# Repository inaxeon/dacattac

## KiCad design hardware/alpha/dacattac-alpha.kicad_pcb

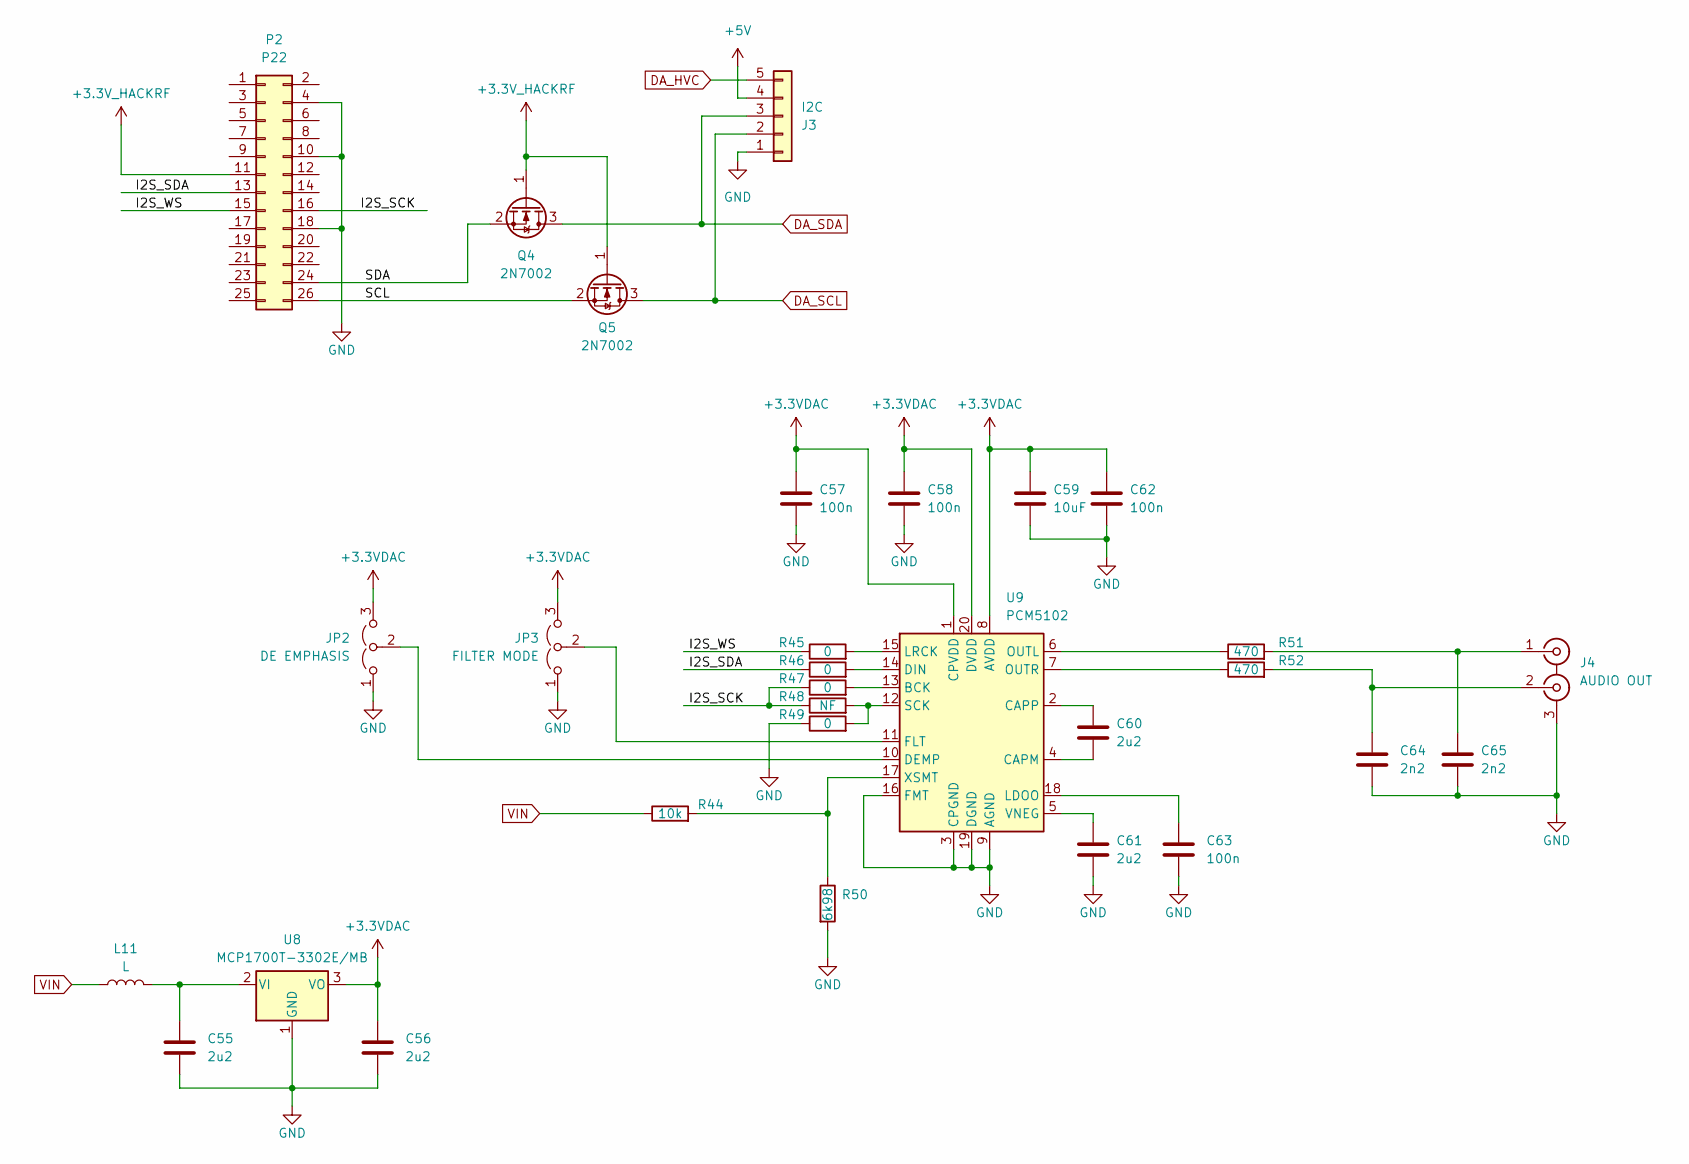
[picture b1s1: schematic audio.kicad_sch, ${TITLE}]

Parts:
C55, C56, C60, C61: 2u2; C_0603_1608Metric
C57, C58, C62, C63: 100n; C_0603_1608Metric
C59: 10uF; C_1210_3225Metric
C64, C65: 2n2; C_0603_1608Metric
J3: I2C; Molex_KK-254_AE-6410-05A_1x05_P2.54mm_Vertical
J4: AUDIO OUT; PJRAN2X1U01X
JP2: DE EMPHASIS; SolderJumper-3_P1.3mm_Open_Pad1.0x1.5mm
JP3: FILTER MODE; SolderJumper-3_P1.3mm_Open_Pad1.0x1.5mm
L11: L; L_1210_3225Metric
P2: P22; GSG-HEADER-2x13
Q4, Q5: 2N7002; SOT-23
R44: 10k; R_0603_1608Metric
R45, R46, R47, R49: 0; R_0603_1608Metric
R48: NF; R_0603_1608Metric
R50: 6k98; R_0603_1608Metric
R51, R52: 470; R_0603_1608Metric
U8: MCP1700T-3302E/MB; SOT-89-3
U9: PCM5102; TSSOP-20_4.4x6.5mm_P0.65mm

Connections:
+3.3VDAC: C56.1, C57.1, C58.1, C59.1, C62.1, JP2.3 (B), JP3.3 (B), U8.3 (VO), U9.1 (CPVDD), U9.8 (AVDD), U9.20 (DVDD)
+3.3V_HACKRF: P2.11, Q4.1 (G), Q5.1 (G); also elsewhere on the board
+5V: J3.4; also elsewhere on the board
/audio/I2S_SCK: P2.16, R47.1, R48.1
/audio/I2S_SDA: P2.13, R46.1
/audio/I2S_WS: P2.15, R45.1
/audio/SCL: P2.26, Q5.2 (S)
/audio/SDA: P2.24, Q4.2 (S)
DA_HVC: J3.5; also elsewhere on the board
DA_SCL: J3.2, Q5.3 (D); also elsewhere on the board
DA_SDA: J3.3, Q4.3 (D); also elsewhere on the board
GND: C55.2, C56.2, C57.2, C58.2, C59.2, C61.2, C62.2, C63.2, C64.2, C65.2, J3.1, J4.3 (EXT), JP2.1 (A), JP3.1 (A), P2.4, P2.10, P2.18, R49.1, R50.2, U8.1 (GND), U9.3 (CPGND), U9.9 (AGND), U9.16 (FMT), U9.19 (DGND); also elsewhere on the board
unnamed: C65.1, J4.1 (IN1), R51.2
unnamed: C64.1, J4.2 (IN2), R52.2
unnamed: JP2.2 (C), U9.10 (DEMP)
unnamed: JP3.2 (C), U9.11 (FLT)
unnamed: C55.1, L11.2, U8.2 (VI)
unnamed: R47.2, U9.13 (BCK)
unnamed: C60.2, U9.4 (CAPM)
unnamed: C60.1, U9.2 (CAPP)
unnamed: R46.2, U9.14 (DIN)
unnamed: C63.1, U9.18 (LDOO)
unnamed: R45.2, U9.15 (LRCK)
unnamed: R51.1, U9.6 (OUTL)
unnamed: R52.1, U9.7 (OUTR)
unnamed: R48.2, R49.2, U9.12 (SCK)
unnamed: C61.1, U9.5 (VNEG)
unnamed: R44.2, R50.1, U9.17 (XSMT)
VIN: L11.1, R44.1; also elsewhere on the board

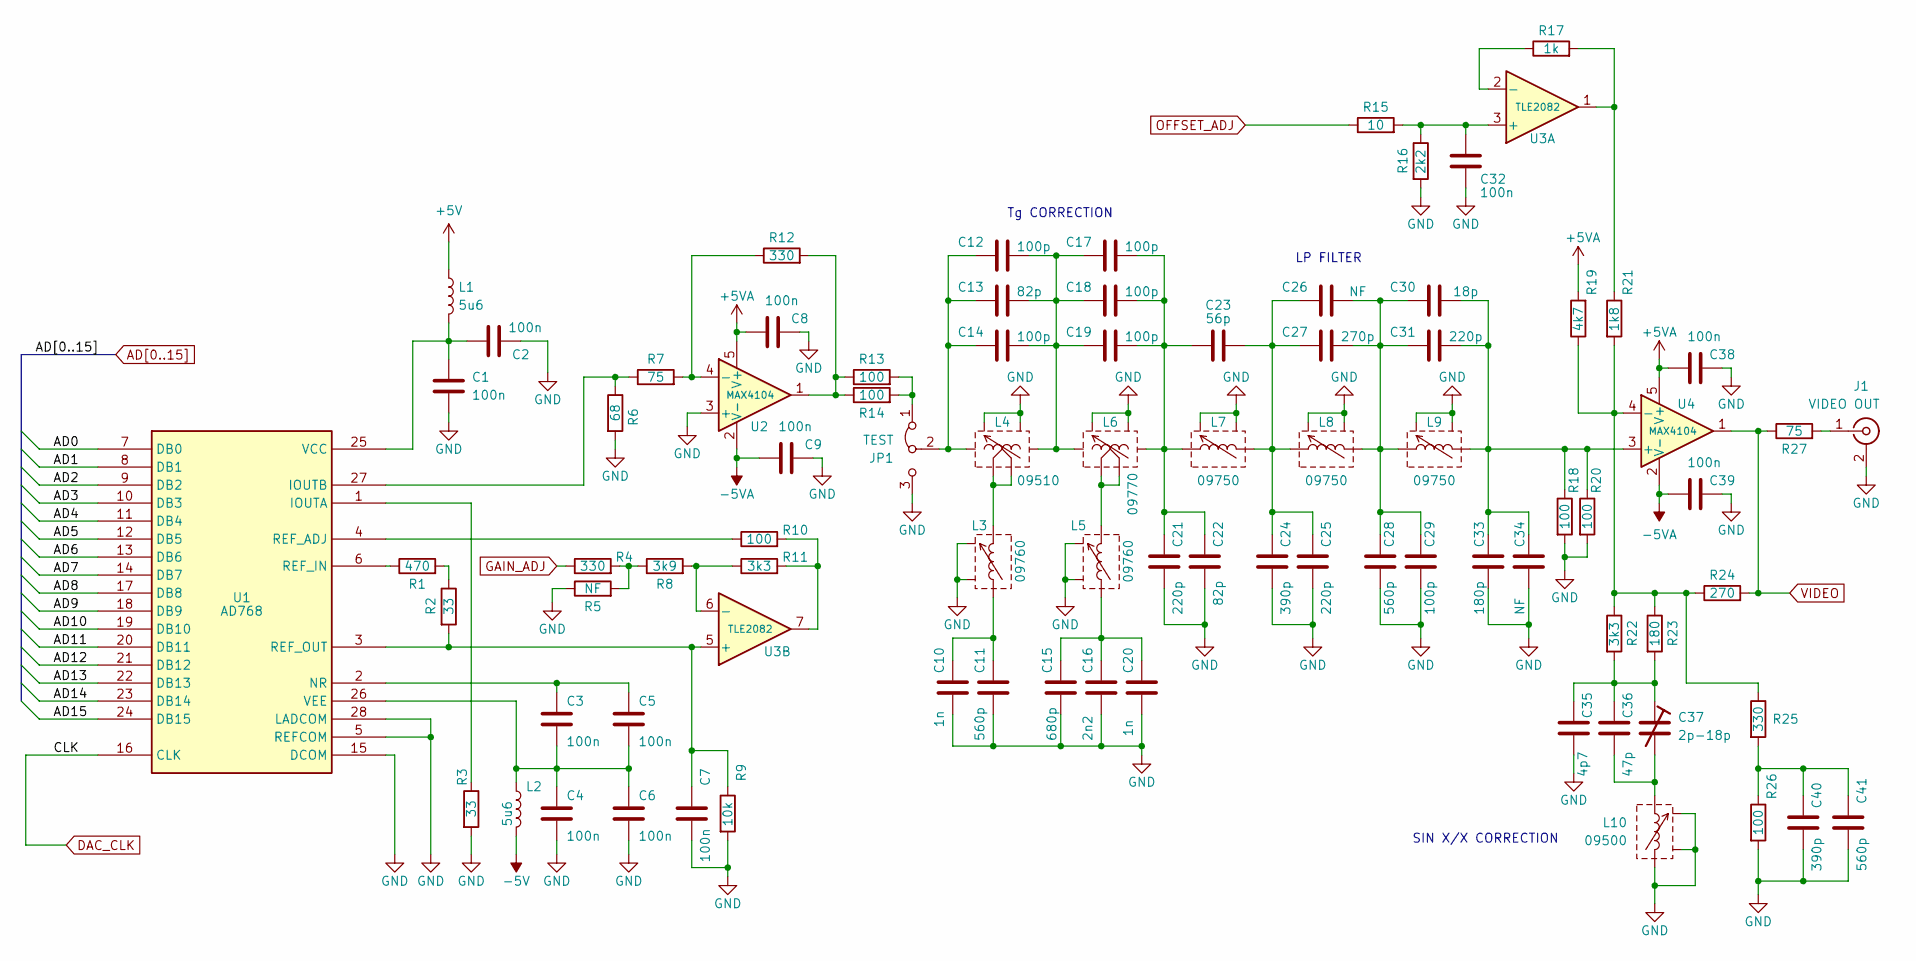
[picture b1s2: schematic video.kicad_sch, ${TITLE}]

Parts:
C1, C2, C3, C4, C5, C6, C7, C8, C9, C32, C38, C39: 100n; C_0603_1608Metric
C10, C20: 1n; C_0603_1608Metric
C11, C28, C41: 560p; C_0603_1608Metric
C12, C14, C17, C18, C19, C29: 100p; C_0603_1608Metric
C13, C22: 82p; C_0603_1608Metric
C15: 680p; C_0603_1608Metric
C16: 2n2; C_0603_1608Metric
C21, C25, C31: 220p; C_0603_1608Metric
C23: 56p; C_0603_1608Metric
C24, C40: 390p; C_0603_1608Metric
C26, C34: NF; C_0603_1608Metric
C27: 270p; C_0603_1608Metric
C30: 18p; C_0603_1608Metric
C33: 180p; C_0603_1608Metric
C35: 4p7; C_0603_1608Metric
C36: 47p; C_0603_1608Metric
C37: 2p-18p; BFC2808xxxxx
J1: VIDEO OUT; 731010120
JP1: TEST; PinHeader_1x03_P2.54mm_Vertical
L1, L2: 5u6; L_1210_3225Metric
L3, L5: 09760; NEOSID_7MM
L4: 09510; NEOSID_7MM
L6: 09770; NEOSID_7MM
L7, L8, L9: 09750; NEOSID_7MM
L10: 09500; NEOSID_7MM
R1: 470; R_0603_1608Metric
R2, R3: 33; R_0603_1608Metric
R4, R12, R25: 330; R_0603_1608Metric
R5: NF; R_0603_1608Metric
R6: 68; R_0603_1608Metric
R7, R27: 75; R_0603_1608Metric
R8: 3k9; R_0603_1608Metric
R9: 10k; R_0603_1608Metric
R10, R13, R14, R18, R20, R26: 100; R_0603_1608Metric
R11, R22: 3k3; R_0603_1608Metric
R15: 10; R_0603_1608Metric
R16: 2k2; R_0603_1608Metric
R17: 1k; R_0603_1608Metric
R19: 4k7; R_0603_1608Metric
R21: 1k8; R_0603_1608Metric
R23: 180; R_0603_1608Metric
R24: 270; R_0603_1608Metric
U1: AD768; SOIC-28W_7.5x18.7mm_P1.27mm
U2, U4: MAX4104; SOT-23-5
U3: TLE2082; SOIC-8_3.9x4.9mm_P1.27mm

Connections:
+5V: L1.1; also elsewhere on the board
+5VA: C8.1, C38.1, R19.2, U2.5 (V+), U4.5 (V+); also elsewhere on the board
-5V: L2.2; also elsewhere on the board
-5VA: C9.1, C39.1, U2.2 (V-), U4.2 (V-); also elsewhere on the board
/video/ADAC+: C1.2, C2.2, L1.2, U1.25 (VCC)
/video/ADAC-: C3.2, C4.1, C5.1, C6.1, L2.1, U1.26 (VEE)
AD0: U1.7 (DB0); also elsewhere on the board
AD1: U1.8 (DB1); also elsewhere on the board
AD2: U1.9 (DB2); also elsewhere on the board
AD3: U1.10 (DB3); also elsewhere on the board
AD4: U1.11 (DB4); also elsewhere on the board
AD5: U1.12 (DB5); also elsewhere on the board
AD6: U1.13 (DB6); also elsewhere on the board
AD7: U1.14 (DB7); also elsewhere on the board
AD8: U1.17 (DB8); also elsewhere on the board
AD9: U1.18 (DB9); also elsewhere on the board
AD10: U1.19 (DB10); also elsewhere on the board
AD11: U1.20 (DB11); also elsewhere on the board
AD12: U1.21 (DB12); also elsewhere on the board
AD13: U1.22 (DB13); also elsewhere on the board
AD14: U1.23 (DB14); also elsewhere on the board
AD15: U1.24 (DB15); also elsewhere on the board
DAC_CLK: U1.16 (CLK); also elsewhere on the board
GAIN_ADJ: R4.1; also elsewhere on the board
GND: C1.1, C2.1, C4.2, C6.2, C7.2, C8.2, C9.2, C10.2, C11.2, C15.2, C16.2, C20.2, C21.2, C22.2, C24.2, C25.2, C28.2, C29.2, C32.2, C33.2, C34.2, C35.2, C38.2, C39.2, C40.2, C41.2, J1.2 (Ext), JP1.3 (B), L3.6, L4.6, L5.6, L6.6, L7.6, L8.6, L9.6, L10.4, L10.6, R3.2, R5.1, R6.2, R9.2, R16.2, R18.2, R20.2, R26.2, U1.5 (REFCOM), U1.15 (DCOM), U1.28 (LADCOM), U2.3 (+); also elsewhere on the board
unnamed: C10.1, C11.1, L3.4
unnamed: C12.2, C13.2, C14.2, C17.1, C18.1, C19.1, L4.1, L6.5
unnamed: C15.1, C16.1, C20.1, L5.4
unnamed: C17.2, C18.2, C19.2, C21.1, C22.1, C23.1, L6.1, L7.1
unnamed: C23.2, C24.1, C25.1, C26.1, C27.1, L7.4, L8.1
unnamed: C26.2, C27.2, C28.1, C29.1, C30.1, C31.1, L8.4, L9.1
unnamed: C35.1, C36.1, C37.1, R22.2, R23.2
unnamed: C36.2, C37.2, L10.1
unnamed: C40.1, C41.1, R25.2, R26.1
unnamed: J1.1 (In), R27.2
unnamed: JP1.1 (A), R13.2, R14.2
unnamed: C12.1, C13.1, C14.1, JP1.2 (C), L4.5
unnamed: L3.1, L4.2, L4.4
unnamed: L5.1, L6.2, L6.4
unnamed: R1.2, R2.1
unnamed: R4.2, R5.2, R8.1
unnamed: R10.2, R11.2, U3.7
unnamed: R12.2, R13.1, R14.1, U2.1
unnamed: R17.2, R21.1, U3.1
unnamed: R3.1, U1.1 (IOUTA)
unnamed: R6.1, R7.1, U1.27 (IOUTB)
unnamed: C3.1, C5.2, U1.2 (NR)
unnamed: R10.1, U1.4 (REF_ADJ)
unnamed: R1.1, U1.6 (REF_IN)
unnamed: C7.1, R2.2, R9.1, U1.3 (REF_OUT), U3.5 (+)
unnamed: R7.2, R12.1, U2.4 (-)
unnamed: C32.1, R15.2, R16.1, U3.3 (+)
unnamed: R17.1, U3.2 (-)
unnamed: R8.2, R11.1, U3.6 (-)
unnamed: C30.2, C31.2, C33.1, C34.1, L9.4, R18.1, R20.1, U4.3 (+)
unnamed: R19.1, R21.2, R22.1, R23.1, R24.1, R25.1, U4.4 (-)
OFFSET_ADJ: R15.1; also elsewhere on the board
VIDEO: R24.2, R27.1, U4.1; also elsewhere on the board

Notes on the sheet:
LP FILTER
Tg CORRECTION
SIN X/X CORRECTION

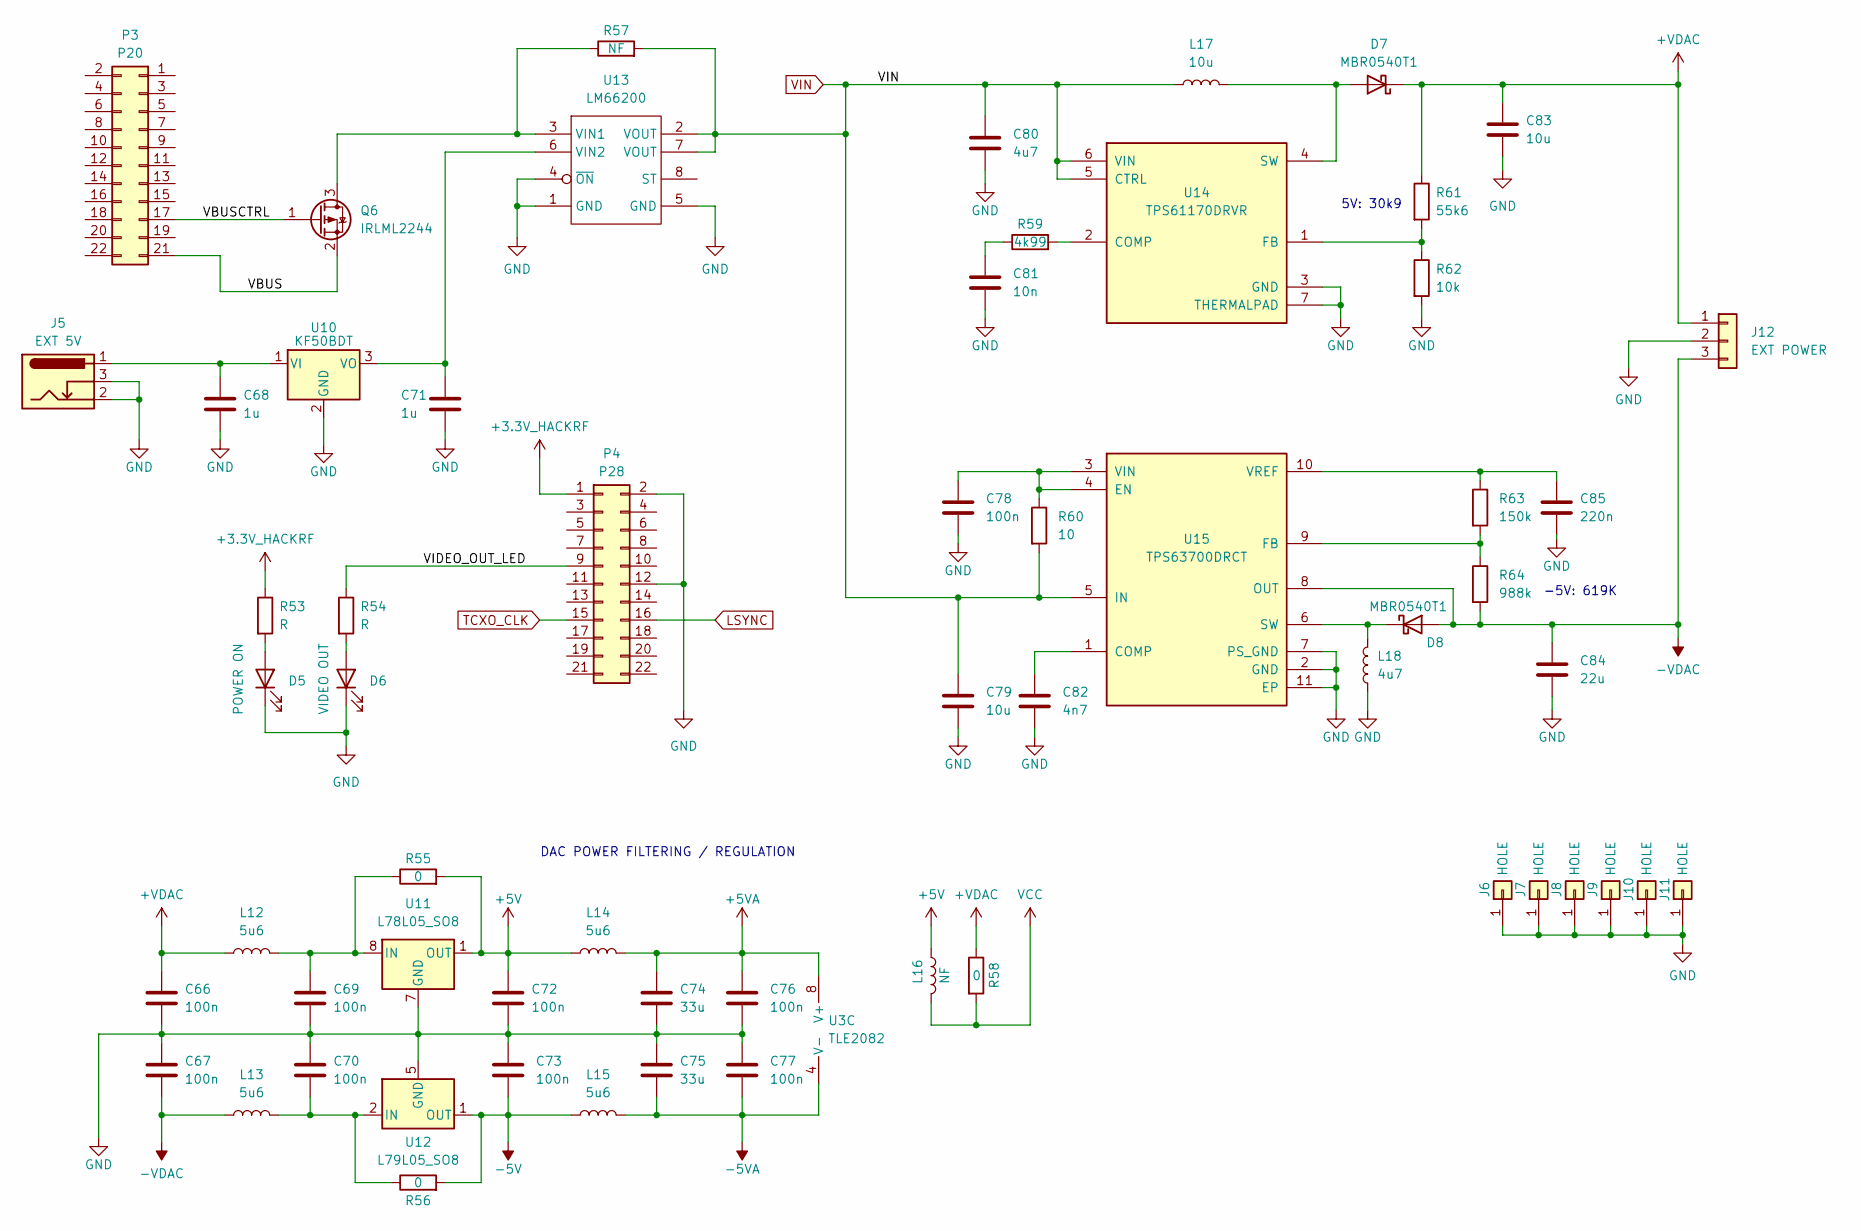
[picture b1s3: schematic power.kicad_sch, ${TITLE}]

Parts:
C66, C67, C69, C70, C72, C73, C76, C77, C78: 100n; C_0603_1608Metric
C68, C71: 1u; C_0603_1608Metric
C74, C75: 33u; C_1210_3225Metric
C79, C83: 10u; C_1210_3225Metric
C80: 4u7; C_1210_3225Metric
C81: 10n; C_0603_1608Metric
C82: 4n7; C_0603_1608Metric
C84: 22u; C_1210_3225Metric
C85: 220n; C_0603_1608Metric
D5: POWER ON; LED_0805_2012Metric
D6: VIDEO OUT; LED_0805_2012Metric
D7, D8: MBR0540T1; D_SOD-123
J5: EXT 5V; BarrelJack_Horizontal
J6, J7, J8, J9, J10, J11: HOLE; GSG-HOLE126MIL-COPPER
J12: EXT POWER; Molex_KK-254_AE-6410-03A_1x03_P2.54mm_Vertical
L12, L13, L14, L15: 5u6; L_1210_3225Metric
L16: NF; L_1210_3225Metric
L17: 10u; L_1210_3225Metric
L18: 4u7; L_1210_3225Metric
P3: P20; GSG-HEADER-2x11
P4: P28; GSG-HEADER-2x11
Q6: IRLML2244; SOT-23
R53, R54: R; R_0603_1608Metric
R55, R56, R58: 0; R_0603_1608Metric
R57: NF; R_0603_1608Metric
R59: 4k99; R_0603_1608Metric
R60: 10; R_0603_1608Metric
R61: 55k6; R_0603_1608Metric
R62: 10k; R_0603_1608Metric
R63: 150k; R_0603_1608Metric
R64: 988k; R_0603_1608Metric
U3: TLE2082; SOIC-8_3.9x4.9mm_P1.27mm
U10: KF50BDT; TO-252-2
U11: L78L05_SO8; SOIC-8_3.9x4.9mm_P1.27mm
U12: L79L05_SO8; SOIC-8_3.9x4.9mm_P1.27mm
U13: LM66200; SOT-583-8
U14: TPS61170DRVR; SON65P200X200X80-7N
U15: TPS63700DRCT; VREG_V62_16624-01YE

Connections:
+3.3V_HACKRF: P4.1, R53.1; also elsewhere on the board
+5V: C72.1, L14.1, L16.1, R55.2, U11.1 (OUT); also elsewhere on the board
+5VA: C74.1, C76.1, L14.2, U3.8 (V+); also elsewhere on the board
+VDAC: C66.1, C83.1, D7.1 (K), J12.1, L12.1, R58.1, R61.1
-5V: C73.2, L15.1, R56.2, U12.1 (OUT); also elsewhere on the board
-5VA: C75.2, C77.2, L15.2, U3.4 (V-); also elsewhere on the board
-VDAC: C67.2, C84.1, D8.2 (A), J12.3, L13.1, R64.2, U15.8 (OUT); also elsewhere on the board
/power/VBUS: P3.21, Q6.2 (S)
/power/VBUSCTRL: P3.17, Q6.1 (G)
/power/VIDEO_OUT_LED: P4.9, R54.1
GND: C66.2, C67.1, C68.2, C69.2, C70.1, C71.2, C72.2, C73.1, C74.2, C75.1, C76.2, C77.1, C78.2, C79.2, C80.2, C81.2, C82.2, C83.2, C84.2, C85.2, D5.1 (K), D6.1 (K), J5.2, J5.3, J6.1, J7.1, J8.1, J9.1, J10.1, J11.1, J12.2, L18.1, P4.2, P4.12, R62.2, U10.2 (GND), U11.2 (GND), U11.3 (GND), U11.6 (GND), U11.7 (GND), U12.5 (GND), U13.1 (GND), U13.4 (~ON), U13.5 (GND), U14.3 (GND), U14.7 (THERMALPAD), U15.2 (GND), U15.7 (PS_GND), U15.11 (EP); also elsewhere on the board
LSYNC: P4.16; also elsewhere on the board
unnamed: C70.2, L13.2, R56.1, U12.2 (IN), U12.3 (IN), U12.6 (IN), U12.7 (IN)
unnamed: C81.1, R59.1
unnamed: D5.2 (A), R53.2
unnamed: D6.2 (A), R54.2
unnamed: D7.2 (A), L17.2, U14.4 (SW)
unnamed: D8.1 (K), L18.2, U15.6 (SW)
unnamed: Q6.3 (D), R57.1, U13.3 (VIN1)
unnamed: C68.1, J5.1, U10.1 (VI)
unnamed: C71.1, U10.3 (VO), U13.6 (VIN2)
unnamed: C69.1, L12.2, R55.1, U11.8 (IN)
unnamed: R59.2, U14.2 (COMP)
unnamed: R61.2, R62.1, U14.1 (FB)
unnamed: C82.1, U15.1 (COMP)
unnamed: C78.1, R60.1, U15.3 (VIN), U15.4 (EN)
unnamed: R63.2, R64.1, U15.9 (FB)
unnamed: C85.1, R63.1, U15.10 (VREF)
TCXO_CLK: P4.15; also elsewhere on the board
VCC: L16.2, R58.2; also elsewhere on the board
VIN: C79.1, C80.1, L17.1, R57.2, R60.2, U13.2 (VOUT), U13.7 (VOUT), U14.5 (CTRL), U14.6 (VIN), U15.5 (IN); also elsewhere on the board

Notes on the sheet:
DAC POWER FILTERING / REGULATION
-5V: 619K
5V: 30k9

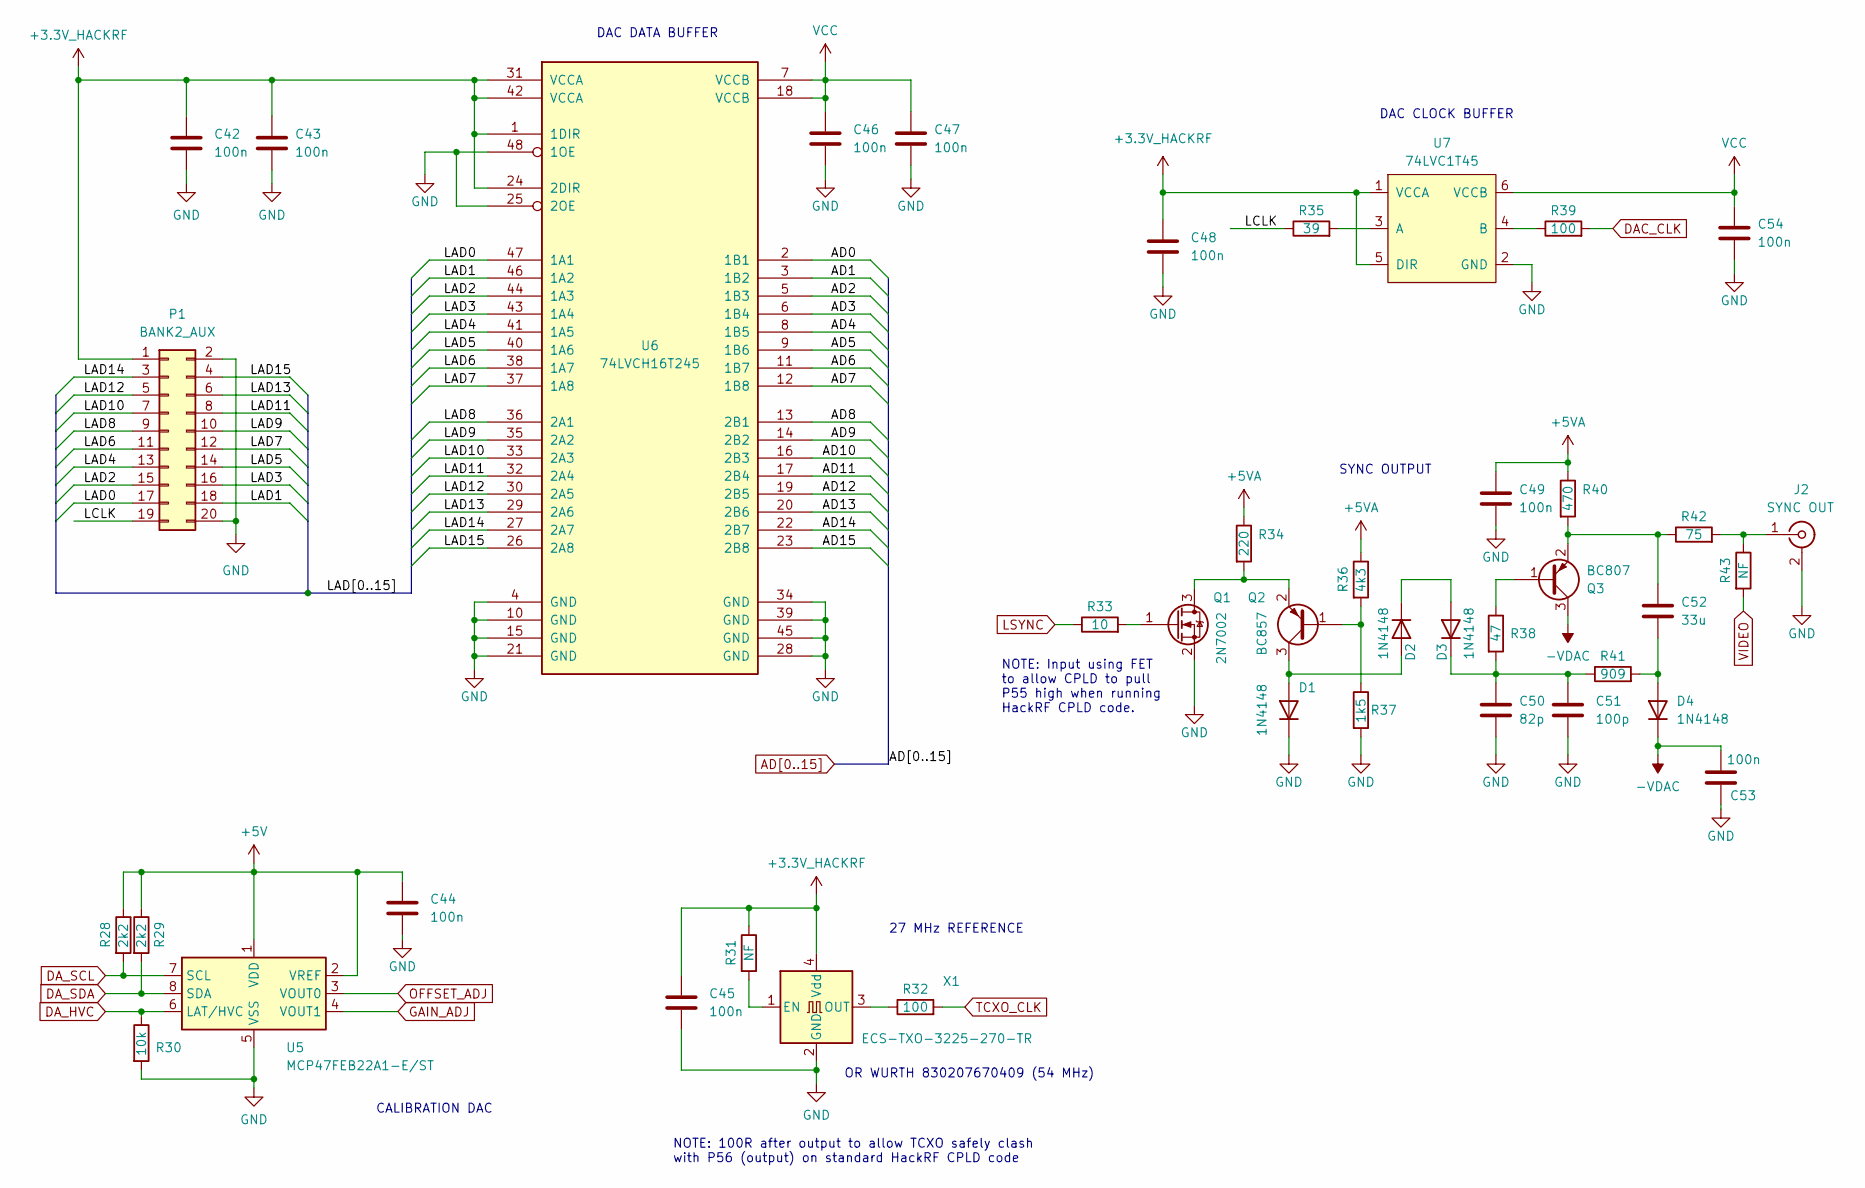
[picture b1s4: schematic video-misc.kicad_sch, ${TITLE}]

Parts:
C42, C43, C44, C45, C46, C47, C48, C49, C53, C54: 100n; C_0603_1608Metric
C50: 82p; C_0603_1608Metric
C51: 100p; C_0603_1608Metric
C52: 33u; C_1210_3225Metric
D1, D2, D3, D4: 1N4148; D_SOD-123
J2: SYNC OUT; 731010120
P1: BANK2_AUX; GSG-HEADER-2x10
Q1: 2N7002; SOT-23
Q2: BC857; SOT-23
Q3: BC807; SOT-23
R28, R29: 2k2; R_0603_1608Metric
R30: 10k; R_0603_1608Metric
R31, R43: NF; R_0603_1608Metric
R32, R39: 100; R_0603_1608Metric
R33: 10; R_0603_1608Metric
R34: 220; R_0603_1608Metric
R35: 39; R_0603_1608Metric
R36: 4k3; R_0603_1608Metric
R37: 1k5; R_0603_1608Metric
R38: 47; R_0603_1608Metric
R40: 470; R_0603_1608Metric
R41: 909; R_0603_1608Metric
R42: 75; R_0603_1608Metric
U5: MCP47FEB22A1-E/ST; TSSOP-8_4.4x3mm_P0.65mm
U6: 74LVCH16T245; TSSOP-48_6.1x12.5mm_P0.5mm
U7: 74LVC1T45; SOT-23-6
X1: ECS-TXO-3225-270-TR; Oscillator_SMD_EuroQuartz_XO32-4Pin_3.2x2.5mm

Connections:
+3.3V_HACKRF: C42.1, C43.1, C45.1, C48.1, P1.1, R31.1, U6.1 (1DIR), U6.24 (2DIR), U6.31 (VCCA), U6.42 (VCCA), U7.1 (VCCA), U7.5 (DIR), X1.4 (Vdd); also elsewhere on the board
+5V: C44.1, R28.1, R29.1, U5.1 (VDD), U5.2 (VREF); also elsewhere on the board
+5VA: C49.1, R34.1, R36.1, R40.1; also elsewhere on the board
-VDAC: C53.2, D4.1 (K), Q3.3 (C); also elsewhere on the board
/video-misc/LAD0: P1.17, U6.47 (1A1)
/video-misc/LAD1: P1.18, U6.46 (1A2)
/video-misc/LAD2: P1.15, U6.44 (1A3)
/video-misc/LAD3: P1.16, U6.43 (1A4)
/video-misc/LAD4: P1.13, U6.41 (1A5)
/video-misc/LAD5: P1.14, U6.40 (1A6)
/video-misc/LAD6: P1.11, U6.38 (1A7)
/video-misc/LAD7: P1.12, U6.37 (1A8)
/video-misc/LAD8: P1.9, U6.36 (2A1)
/video-misc/LAD9: P1.10, U6.35 (2A2)
/video-misc/LAD10: P1.7, U6.33 (2A3)
/video-misc/LAD11: P1.8, U6.32 (2A4)
/video-misc/LAD12: P1.5, U6.30 (2A5)
/video-misc/LAD13: P1.6, U6.29 (2A6)
/video-misc/LAD14: P1.3, U6.27 (2A7)
/video-misc/LAD15: P1.4, U6.26 (2A8)
/video-misc/LCLK: P1.19, R35.1
AD0: U6.2 (1B1); also elsewhere on the board
AD1: U6.3 (1B2); also elsewhere on the board
AD2: U6.5 (1B3); also elsewhere on the board
AD3: U6.6 (1B4); also elsewhere on the board
AD4: U6.8 (1B5); also elsewhere on the board
AD5: U6.9 (1B6); also elsewhere on the board
AD6: U6.11 (1B7); also elsewhere on the board
AD7: U6.12 (1B8); also elsewhere on the board
AD8: U6.13 (2B1); also elsewhere on the board
AD9: U6.14 (2B2); also elsewhere on the board
AD10: U6.16 (2B3); also elsewhere on the board
AD11: U6.17 (2B4); also elsewhere on the board
AD12: U6.19 (2B5); also elsewhere on the board
AD13: U6.20 (2B6); also elsewhere on the board
AD14: U6.22 (2B7); also elsewhere on the board
AD15: U6.23 (2B8); also elsewhere on the board
DAC_CLK: R39.2; also elsewhere on the board
DA_HVC: R30.1, U5.6 (LAT/HVC); also elsewhere on the board
DA_SCL: R28.2, U5.7 (SCL); also elsewhere on the board
DA_SDA: R29.2, U5.8 (SDA); also elsewhere on the board
GAIN_ADJ: U5.4 (VOUT1); also elsewhere on the board
GND: C42.2, C43.2, C44.2, C45.2, C46.2, C47.2, C48.2, C49.2, C50.2, C51.2, C53.1, C54.2, D1.1 (K), J2.2 (Ext), P1.2, P1.20, Q1.2 (S), R30.2, R37.2, U5.5 (VSS), U6.4 (GND), U6.10 (GND), U6.15 (GND), U6.21 (GND), U6.25 (2OE), U6.28 (GND), U6.34 (GND), U6.39 (GND), U6.45 (GND), U6.48 (1OE), U7.2 (GND), X1.2 (GND); also elsewhere on the board
LSYNC: R33.1; also elsewhere on the board
unnamed: D1.2 (A), D2.2 (A), Q2.3 (C)
unnamed: D2.1 (K), D3.2 (A)
unnamed: C50.1, C51.1, D3.1 (K), R38.2, R41.1
unnamed: C52.2, D4.2 (A), R41.2
unnamed: J2.1 (In), R42.2, R43.1
unnamed: Q1.3 (D), Q2.2 (E), R34.2
unnamed: Q1.1 (G), R33.2
unnamed: Q2.1 (B), R36.2, R37.1
unnamed: Q3.1 (B), R38.1
unnamed: C52.1, Q3.2 (E), R40.2, R42.1
unnamed: R35.2, U7.3 (A)
unnamed: R39.1, U7.4 (B)
unnamed: R31.2, X1.1 (EN)
unnamed: R32.1, X1.3 (OUT)
OFFSET_ADJ: U5.3 (VOUT0); also elsewhere on the board
TCXO_CLK: R32.2; also elsewhere on the board
VCC: C46.1, C47.1, C54.1, U6.7 (VCCB), U6.18 (VCCB), U7.6 (VCCB); also elsewhere on the board
VIDEO: R43.2; also elsewhere on the board

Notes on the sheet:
CALIBRATION DAC
DAC DATA BUFFER
NOTE: Input using FET to allow CPLD to pull P55 high when running HackRF CPLD code.
OR WURTH 830207670409 (54 MHz)
27 MHz REFERENCE
NOTE: 100R after output to allow TCXO safely clash with P56 (output) on standard HackRF CPLD code
DAC CLOCK BUFFER
SYNC OUTPUT

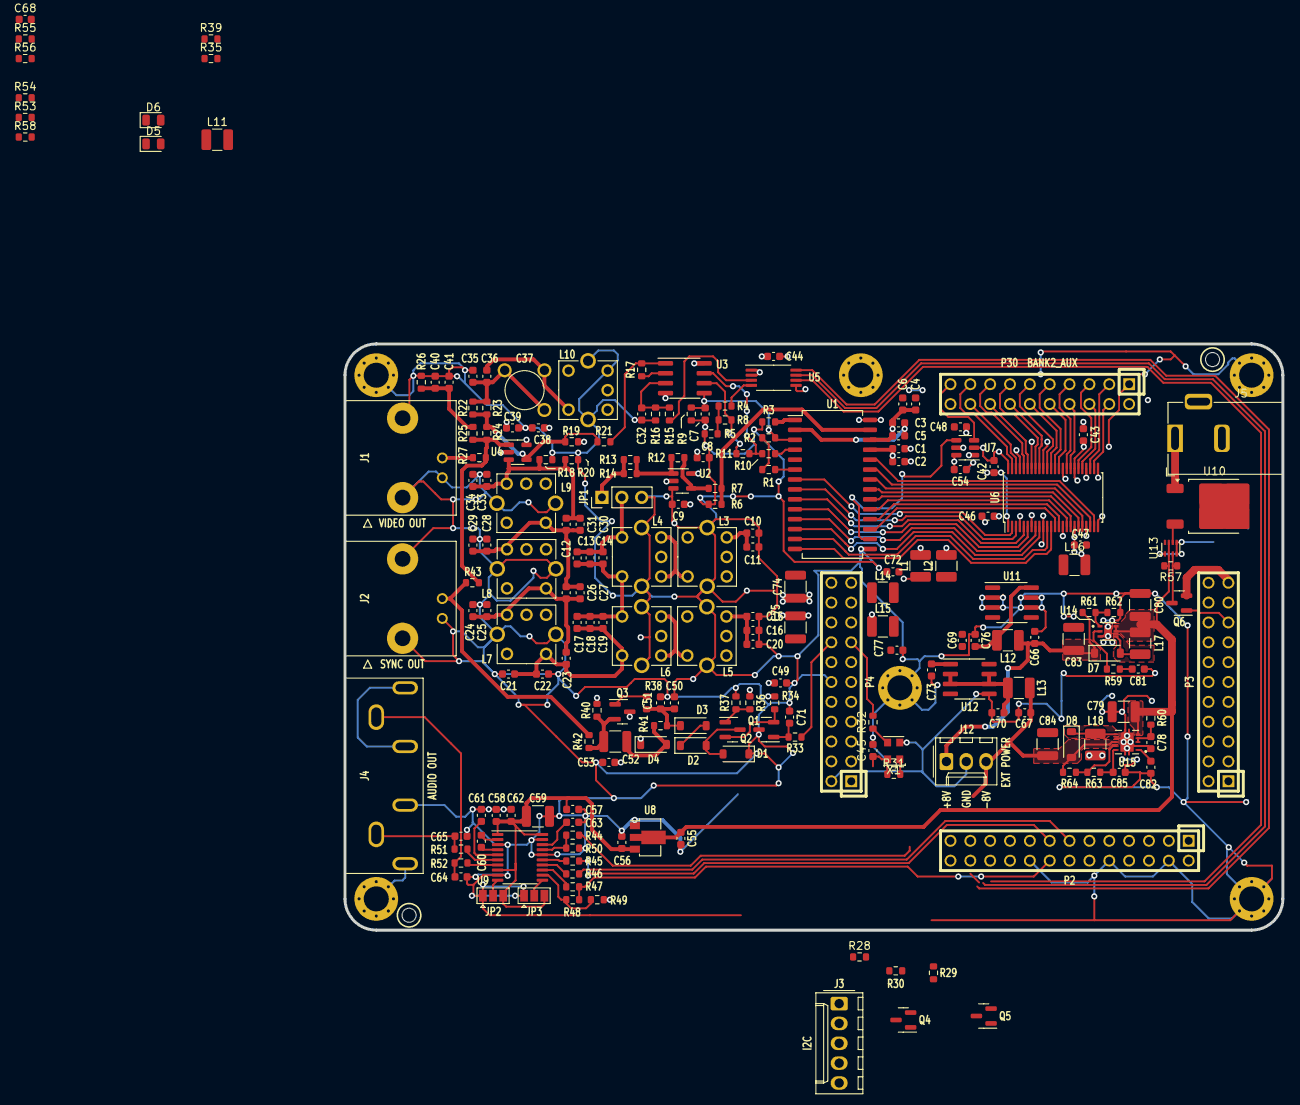
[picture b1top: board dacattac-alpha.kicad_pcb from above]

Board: 4 copper layers, 120.0 x 75.0 mm, 218 parts (0 on the bottom side), 140 nets.

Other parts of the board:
FID1, FID2: FIDUCIAL; GSG-MARK1MM

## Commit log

2024-06-13 Add project
2024-07-29 Added / updated BOm
2024-07-29 BOM WIP
2024-10-06 Update to-do
2024-10-13 Update changes

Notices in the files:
parts and their libraries:
COPYRIGHT: Copyright 2024 Matt Millman
LICENSE: Licensed under the CERN-OHL-P v2
